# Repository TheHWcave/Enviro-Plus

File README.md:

# Enviro-Plus
Experiments in environmental monitoring with Pimoroni's Enviro+ board and Raspberry Pi

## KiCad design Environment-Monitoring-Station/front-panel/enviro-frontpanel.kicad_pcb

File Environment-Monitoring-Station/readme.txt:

Building an environment monitoring station using the Enviro+ board, a Raspberry Pi Zero and a couple of other items.

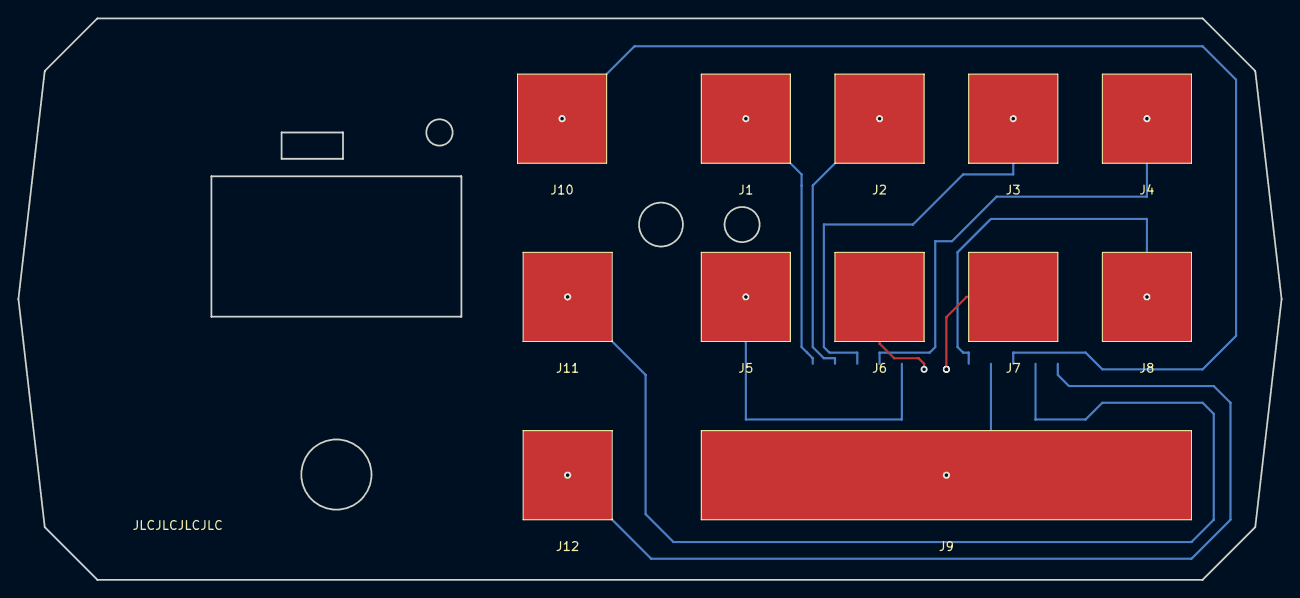
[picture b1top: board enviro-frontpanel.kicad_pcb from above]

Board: 2 copper layers, 144.0 x 64.0 mm, 13 parts (1 on the bottom side), 12 nets.

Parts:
J0: Conn_01x12; 12-pin socket 2.54 SMD
J1, J2, J3, J4, J5, J6, J7, J8, J10, J11, J12: Conn_01x01; Touch pad -single 10x10
J9: Conn_01x01; Touch bar 2200mil

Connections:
unnamed: J0.1, J1.1
unnamed: J0.2, J2.1
unnamed: J0.3, J3.1
unnamed: J0.4, J4.1
unnamed: J0.5, J5.1
unnamed: J0.6, J6.1
unnamed: J0.7, J7.1
unnamed: J0.8, J8.1
unnamed: J0.9, J9.1
unnamed: J0.10, J10.1
unnamed: J0.11, J11.1
unnamed: J0.12, J12.1

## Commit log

2019-07-27 Add files via upload
    removed the correction of BME280 temperature
2019-07-27 Update readme.txt
    Added note, explaining the removal of BME280 temperature correction
2020-06-07 Removed temp. directory
2020-06-07 added Enviroment Monitoring Station initial release
2020-06-28 added software files
2020-06-28 changed repo name for Env.Mon Station
